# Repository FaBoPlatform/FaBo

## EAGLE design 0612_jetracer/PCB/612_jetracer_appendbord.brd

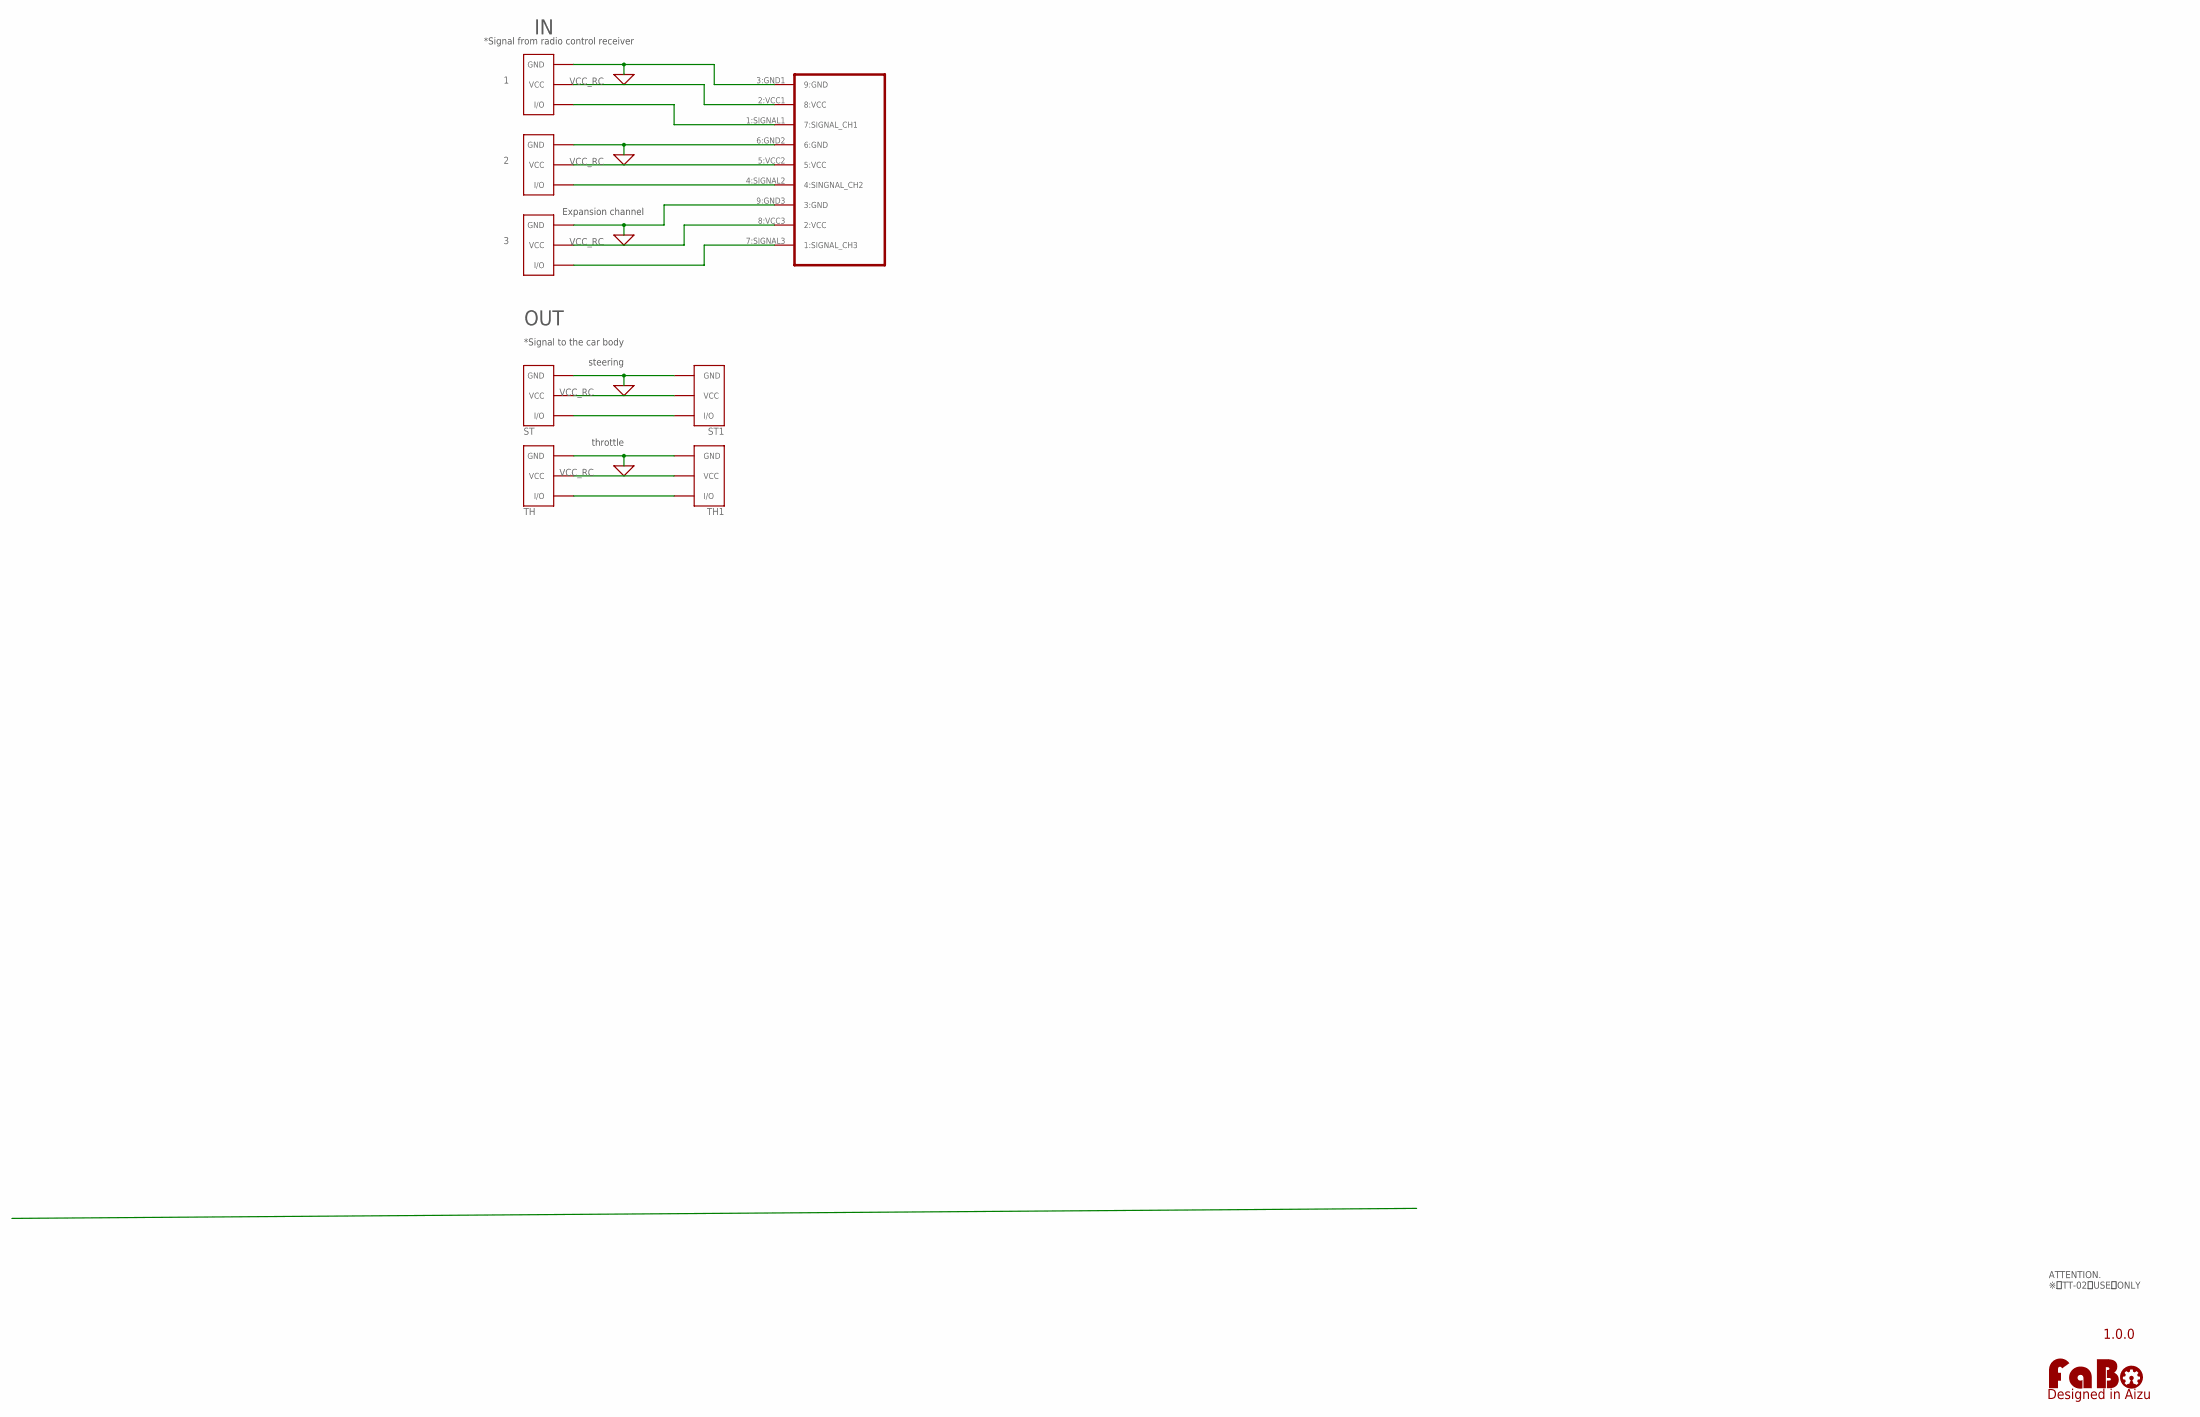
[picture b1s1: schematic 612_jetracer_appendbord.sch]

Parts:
1, 2, 3: FABO_BRICK_3PIN-HEADER; FABO_BRICK_3PIN_HEADER
ST, ST1: FABO_BRICK_3PIN-HEADER; FABO_BRICK_3PIN_HEADER
TH, TH1: FABO_BRICK_3PIN-HEADER; FABO_BRICK_3PIN_HEADER
U$1: RC_9PIN_OUTIN; PNHEADER_2.54_SMT_9PIN_RC_TT01_02
U$5: LOGO_FABO-M; LOGO_FABO_MS

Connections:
0: 1.GND, 2.GND, 3.GND, ST.GND, ST1.GND, TH.GND, TH1.GND, U$1.3:GND1 (9:GND), U$1.6:GND2 (6:GND), U$1.9:GND3 (3:GND)
unnamed: ST.I/O, ST1.I/O
unnamed: TH.I/O, TH1.I/O
unnamed: 3.I/O, U$1.7:SIGNAL3 (1:SIGNAL_CH3)
unnamed: 2.I/O, U$1.4:SIGNAL2 (4:SINGNAL_CH2)
unnamed: 1.I/O, U$1.1:SIGNAL1 (7:SIGNAL_CH1)
VCC_RC: 1.VCC, 2.VCC, 3.VCC, ST.VCC, ST1.VCC, TH.VCC, TH1.VCC, U$1.2:VCC1 (8:VCC), U$1.5:VCC2 (5:VCC), U$1.8:VCC3 (2:VCC)

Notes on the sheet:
1.0.0
*Signal from radio control receiver
*Signal to the car body
steering
throttle
Expansion channel
OUT
ATTENTION. ※ TT-02 USE ONLY

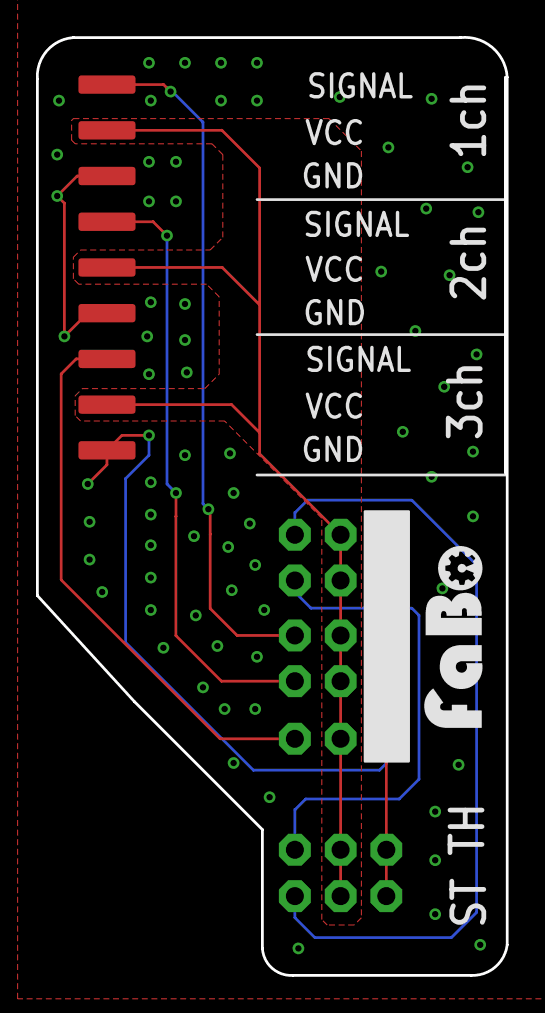
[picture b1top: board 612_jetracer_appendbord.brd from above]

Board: 2 copper layers, 26.1 x 52.1 mm, 10 parts (1 on the bottom side), 7 nets.

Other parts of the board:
U$2: LOGO_FABO_MS

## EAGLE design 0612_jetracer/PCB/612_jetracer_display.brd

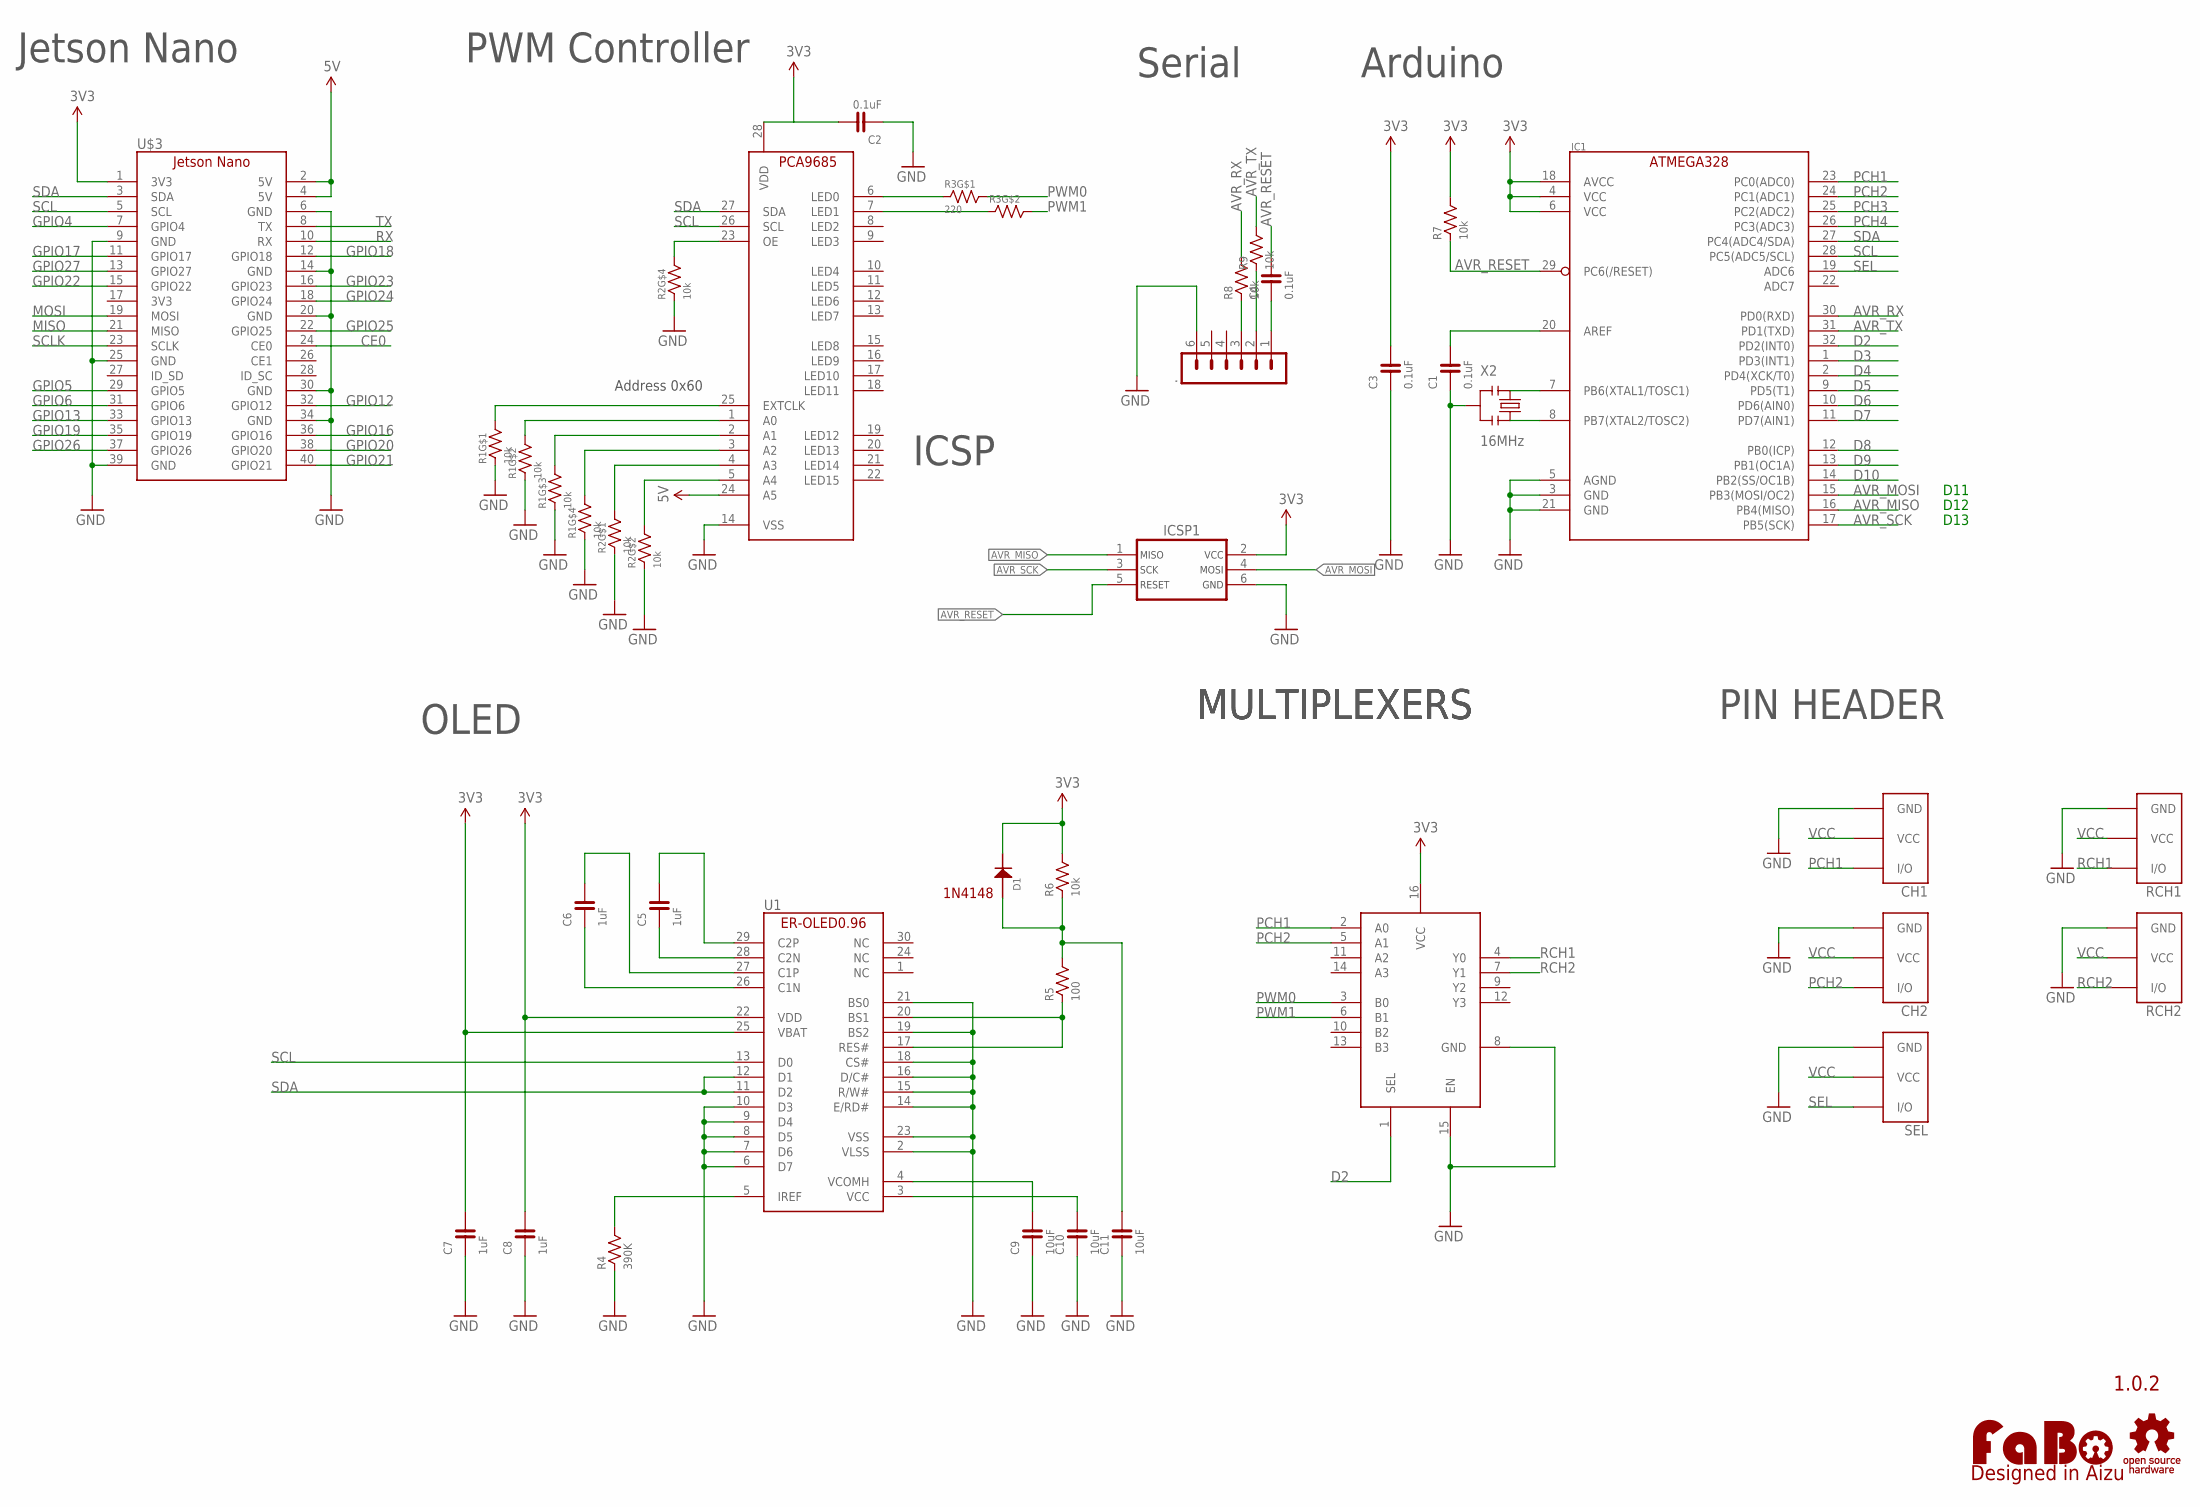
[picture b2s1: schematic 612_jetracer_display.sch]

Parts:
.: MA06-1
C1, C2, C3, C4: 0.1uF; 0603
C5, C6, C7, C8: 1uF; 0603-BOTTOM
C9, C10, C11: 10uF; 0603-BOTTOM
CH1, CH2: FABO_BRICK_3PIN-HEADER; FABO_BRICK_3PIN_HEADER
D1: 1N4148; 1N4148W
IC1: ATMEGA328P-AU; TQFP-32
IC3: MULTIPLEXERSMC74HC157A; TSSOP-16
ICSP1: ICSP_AVR-TC_NOHOLE; TC2030
R1, R2: 10k; EXBV8V
R3: 220; EXBV8V
R4: 390K; 0603-BOTTOM
R5: 100; 0603-BOTTOM
R6: 10k; 0603-BOTTOM
R7, R8, R9: 10k; 0603
RCH1, RCH2: FABO_BRICK_3PIN-HEADER; FABO_BRICK_3PIN_HEADER
SEL: FABO_BRICK_3PIN-HEADER; FABO_BRICK_3PIN_HEADER
U1: ER-OLED0.96-1ER-CON30HT-1; ER-CON30HT-1
U$2: LOGO_OSHW-M_BOTTOM; LOGO_OSHW_M_BOTTOM
U$3: JETSON_NANO
U$5: LOGO_FABO-M; LOGO_FABO_MS
U$9: PCA9685
X2: 16MHz; CSTNE_V_C

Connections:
3V3: C2.2, C3.2, C7.2, D1.CATHODE, IC1.4 (VCC), IC1.6 (VCC), IC1.18 (AVCC), IC3.16 (VCC), ICSP1.2, R6.2, R7.2, U1.25 (VBAT), U$3.1 (3V3), U$9.28 (VDD)
5V: U$3.2 (5V), U$3.4 (5V), U$9.24 (A5)
AVR_MISO: IC1.16 (PB4(MISO)), ICSP1.1
AVR_MOSI: IC1.15 (PB3(MOSI/OC2)), ICSP1.4
AVR_RESET: C4.2, IC1.29 (PC6(/RESET)), ICSP1.5, R7.1
AVR_RX: IC1.30 (PD0(RXD)), R8.2
AVR_SCK: IC1.17 (PB5(SCK)), ICSP1.3
AVR_TX: IC1.31 (PD1(TXD)), R9.2
CE0: U$3.24 (CE0)
D2: IC1.32 (PD2(INT0)), IC3.1 (SEL)
D3: IC1.1 (PD3(INT1))
D4: IC1.2 (PD4(XCK/T0))
D5: IC1.9 (PD5(T1))
D6: IC1.10 (PD6(AIN0))
D7: IC1.11 (PD7(AIN1))
D8: IC1.12 (PB0(ICP))
D9: IC1.13 (PB1(OC1A))
D10: IC1.14 (PB2(SS/OC1B))
GND: ..6, C1.1, C2.1, C3.1, C7.1, C8.1, C9.1, C10.1, C11.1, CH1.GND, CH2.GND, IC1.3 (GND), IC1.5 (AGND), IC1.21 (GND), IC3.8 (GND), IC3.15 (EN), ICSP1.6, R1.1, R1.2 (1), R1.3 (1), R1.4 (1), R2.1, R2.2 (1), R2.4 (1), R4.1, RCH1.GND, RCH2.GND, SEL.GND, U1.2 (VLSS), U1.6 (D7), U1.7 (D6), U1.8 (D5), U1.9 (D4), U1.10 (D3), U1.14 (E/RD#), U1.15 (R/W#), U1.16 (D/C#), U1.18 (CS#), U1.19 (BS2), U1.21 (BS0), U1.23 (VSS), U$3.6 (GND), U$3.9 (GND), U$3.14 (GND), U$3.20 (GND), U$3.25 (GND), U$3.30 (GND), U$3.34 (GND), U$3.39 (GND), U$9.14 (VSS), X2.2
GPIO4: U$3.7 (GPIO4)
GPIO5: U$3.29 (GPIO5)
GPIO6: U$3.31 (GPIO6)
GPIO12: U$3.32 (GPIO12)
GPIO13: U$3.33 (GPIO13)
GPIO16: U$3.36 (GPIO16)
GPIO17: U$3.11 (GPIO17)
GPIO18: U$3.12 (GPIO18)
GPIO19: U$3.35 (GPIO19)
GPIO20: U$3.38 (GPIO20)
GPIO21: U$3.40 (GPIO21)
GPIO22: U$3.15 (GPIO22)
GPIO23: U$3.16 (GPIO23)
GPIO24: U$3.18 (GPIO24)
GPIO25: U$3.22 (GPIO25)
GPIO26: U$3.37 (GPIO26)
GPIO27: U$3.13 (GPIO27)
MISO: U$3.21 (MISO)
MOSI: U$3.19 (MOSI)
unnamed: R3.1, U$9.6 (LED0)
unnamed: R3.2 (1), U$9.7 (LED1)
unnamed: C1.2, IC1.20 (AREF)
unnamed: IC1.8 (PB7(XTAL2/TOSC2)), X2.3
unnamed: ..3, R8.1
unnamed: R2.5 (2), U$9.23 (OE)
unnamed: R1.8 (2), U$9.25 (EXTCLK)
unnamed: R1.7 (2), U$9.1 (A0)
unnamed: R1.6 (2), U$9.2 (A1)
unnamed: R1.5 (2), U$9.3 (A2)
unnamed: R2.8 (2), U$9.4 (A3)
unnamed: R2.7 (2), U$9.5 (A4)
unnamed: C6.2, U1.27 (C1P)
unnamed: IC1.7 (PB6(XTAL1/TOSC1)), X2.1
unnamed: C6.1, U1.26 (C1N)
unnamed: ..2, R9.1
unnamed: ..1, C4.1
unnamed: C5.1, U1.28 (C2N)
unnamed: C5.2, U1.29 (C2P)
unnamed: R4.2, U1.5 (IREF)
unnamed: C9.2, U1.4 (VCOMH)
unnamed: C10.2, U1.3 (VCC)
unnamed: R5.1, U1.17 (RES#), U1.20 (BS1)
unnamed: C11.2, D1.ANODE, R5.2, R6.1
unnamed: C8.2, U1.22 (VDD)
PCH1: CH1.I/O, IC1.23 (PC0(ADC0)), IC3.2 (A0)
PCH2: CH2.I/O, IC1.24 (PC1(ADC1)), IC3.5 (A1)
PCH3: IC1.25 (PC2(ADC2))
PCH4: IC1.26 (PC3(ADC3))
PWM0: IC3.3 (B0), R3.8 (2)
PWM1: IC3.6 (B1), R3.7 (2)
RCH1: IC3.4 (Y0), RCH1.I/O
RCH2: IC3.7 (Y1), RCH2.I/O
RX: U$3.10 (RX)
SCL: IC1.28 (PC5(ADC5/SCL)), U1.13 (D0), U$3.5 (SCL), U$9.26 (SCL)
SCLK: U$3.23 (SCLK)
SDA: IC1.27 (PC4(ADC4/SDA)), U1.11 (D2), U1.12 (D1), U$3.3 (SDA), U$9.27 (SDA)
SEL: IC1.19 (ADC6), SEL.I/O
TX: U$3.8 (TX)
VCC: CH1.VCC, CH2.VCC, RCH1.VCC, RCH2.VCC, SEL.VCC

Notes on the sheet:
1.0.2
Jetson Nano
PWM Controller
MULTIPLEXERS
Address 0x60
1N4148
PIN HEADER
D11
D12
D13
Arduino
Serial
ICSP
OLED

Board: 2 copper layers, 38 parts (0 on the bottom side), 45 nets, no tracks yet.

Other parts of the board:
U$4, U$6: MARK_POINT_3MM

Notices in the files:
parts and their libraries:
FaBo-Template: Released under the Creative Commons Attribution-ShareAlike 4.0 License
https://creativecommons.org/licenses/by-sa/4.0
FaBo-etc: Released under the Creative Commons
